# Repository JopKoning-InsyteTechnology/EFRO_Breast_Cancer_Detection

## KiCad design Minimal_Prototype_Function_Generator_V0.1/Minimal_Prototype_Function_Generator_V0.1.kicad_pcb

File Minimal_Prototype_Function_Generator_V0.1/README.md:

# Module README Template

This `README.md` should be placed inside each module folder (e.g., `Sensors/<Type>/<ModuleName>/`).
It documents the changelog, ordering specifications, and module details for that specific PCB.

---

# Module: `<Module Name>`

## 🏷️ Project Status

Choose **one** badge to indicate the current status of the module:

*(Keep only the relevant badge active in the README. Remove the rest.)*

## 📜 Changelog

| Name  | Date       | Version | Updates                                                 |
| ----- | ---------- | ------- | ------------------------------------------------------- |
| Alice | 01/03/2025 | 1.0     | Initial schematic and layout setup                      |
| Bob   | 15/03/2025 | 1.1     | Updated footprint of sensor, adjusted routing           |
| Carol | 25/03/2025 | 1.1.1   | Fixed silkscreen text overlap, added missing test point |

*(Add rows for each update. Follow semantic versioning: Major.Minor.Patch)*

---

## ⚙️ Ordering Specifications

* **Board thickness**: \<e.g., 0.8 mm>
* **Impedance match**: \<Yes/No, Impedance ohm>
* **Impedance Calculated on** \<e.g., JLC04081H-3313>
* **Base material**: \<e.g., FR4>
* **Color**: \<e.g., Green>
* **Outer copper weight**: \<e.g., 1 oz>
* **Gold fingers**: \<Yes/No, Finish type>
* **Castellated holes**: <Yes/No>
* **Edge plating**: \<Yes/No>
* **Assembly side**: \<Top/Bottom/Both>

---

## 🧩 Module Details

* **Sensor description**: <Short functional description>
* **Used voltage**: \<e.g., 3.3V, Battery, 5V>
* **Used interface**: \<e.g., I2C, SPI, ADC>
* **Active power consumption**: \<Value + unit>
* **Max power consumption**: \<Value + unit>
* **Off mode power consumption**: \<Value + unit>

### Pin definitions

* `<Pin name>` → `<Function>`
* `<Pin name>` → `<Function>`

### Other information

* \<Addresses, special notes, mechanical details, etc.>

---

## 📂 Production References

* See related files in `production/Order_<date>`.

---

### Usage Notes

* Keep this file updated with every version change.
* Ensure production orders reference the correct version noted here.
* Use semantic versioning for updates (Major.Minor.Patch).

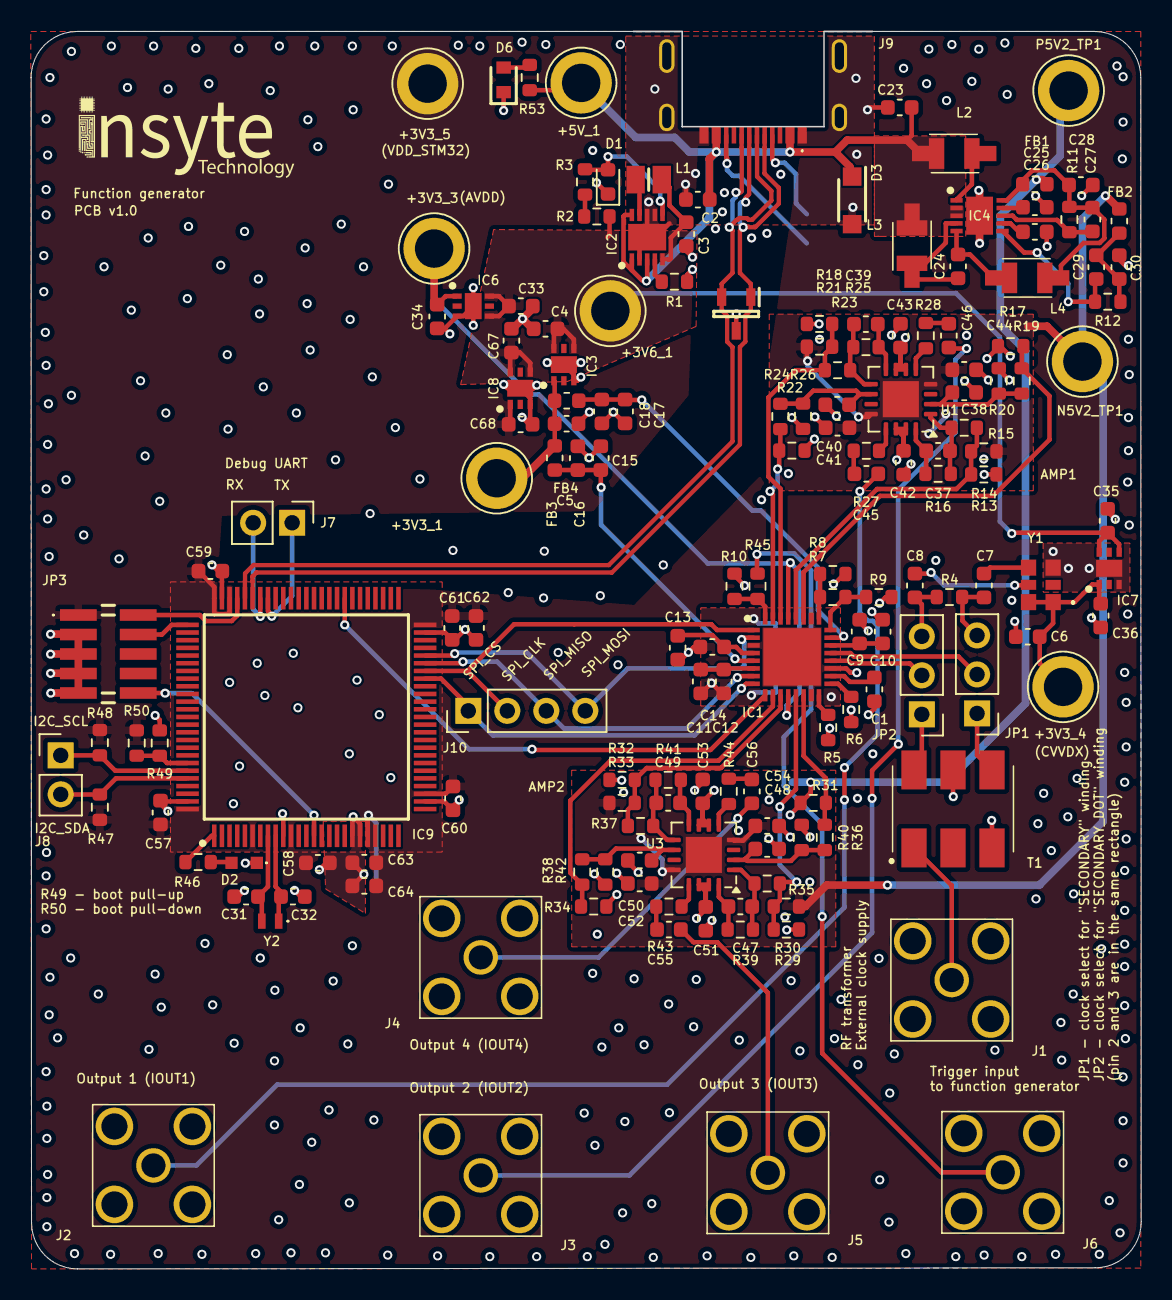
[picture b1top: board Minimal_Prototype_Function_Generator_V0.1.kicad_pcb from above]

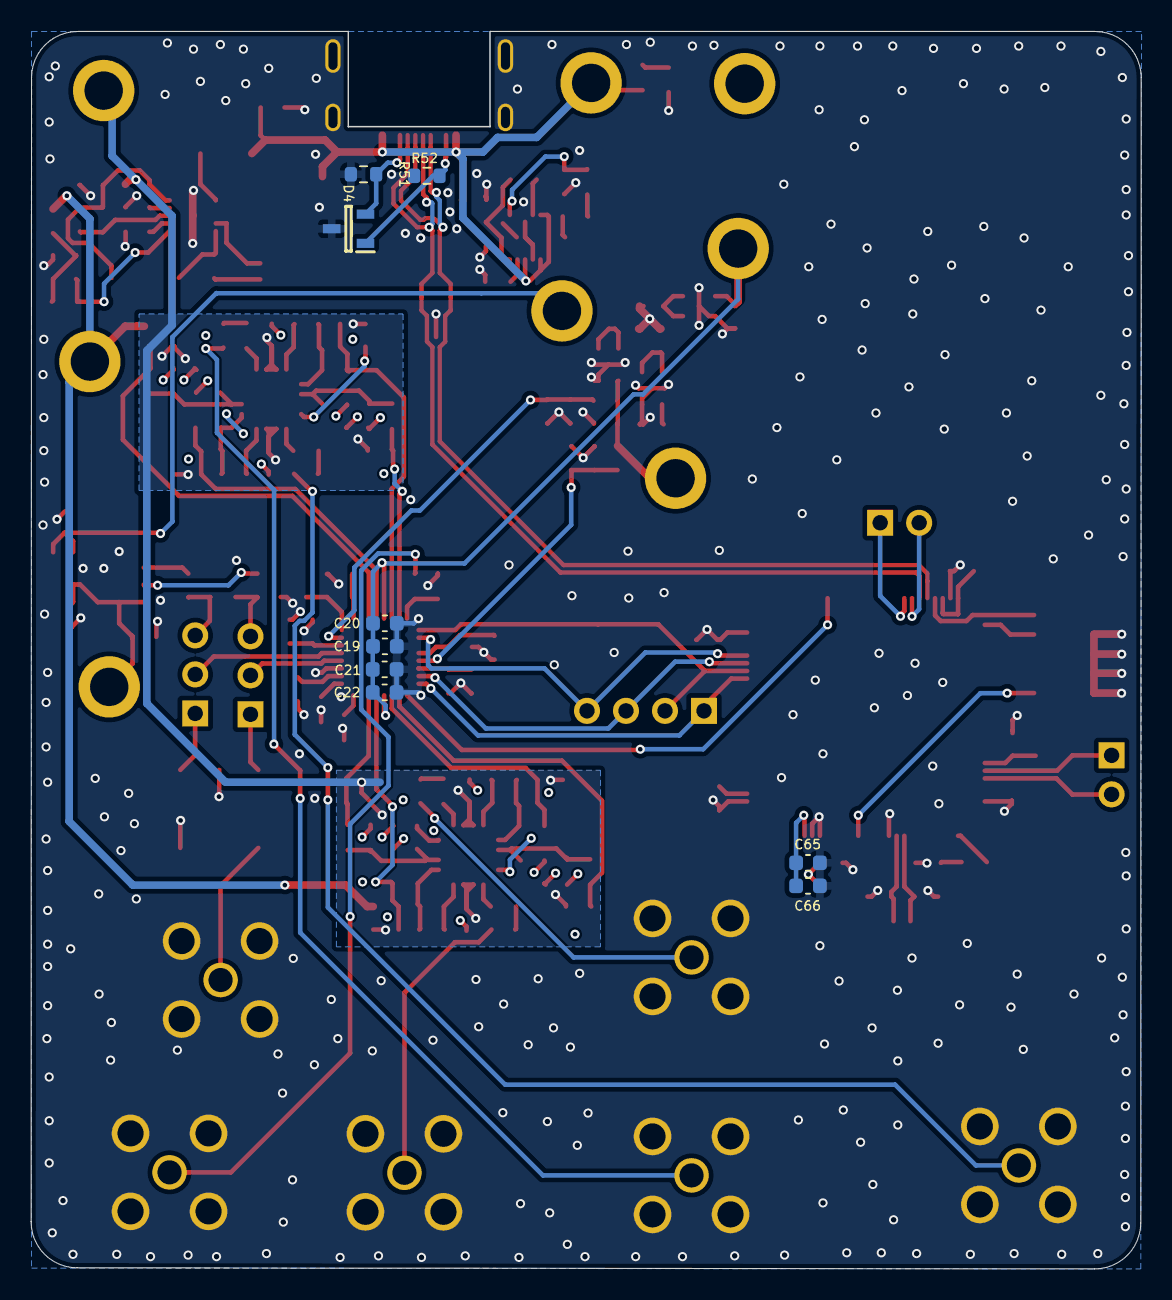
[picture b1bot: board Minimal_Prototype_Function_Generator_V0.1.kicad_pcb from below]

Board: 4 copper layers, 72.3 x 80.6 mm, 170 parts (9 on the bottom side), 97 nets.

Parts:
+3V3_1, +3V3_3, +3V3_4, +3V3_5, +3V6_1, +5V_1: TestPoint; TestPoint_Loop_D3.80mm_Drill2.5mm
C1, C6, C7, C8, C9, C11, C13, C15, C17, C19, C21, C25, C26, C41, C42, C43, C44, C51, C52, C53, C54: 0.1uF; C_0603_1608Metric
C2, C3: 10uF; C_0603_1608Metric
C4, C5, C33, C34, C35, C36, C67, C68: 4.7uF; C_0603_1608Metric
C10, C12, C16, C18, C20, C22: 100pF; C_0603_1608Metric
C14: 0.01uF; C_0603_1608Metric
C23, C28, C30: 2.2uF; C_0603_1608Metric
C24, C45, C46, C55, C56: 1uF; C_0603_1608Metric
C27: 4.7pF; C_0603_1608Metric
C29: 10pF; C_0603_1608Metric
C31, C32: 8pF C0G/NP0 >5%; C_0603_1608Metric
C37, C38, C39, C40, C47, C48, C49, C50: 1.5pF; C_0603_1608Metric
C57, C58, C59, C60, C61, C65: 0.1u; C_0603_1608Metric
C62: 4.7u; C_0603_1608Metric
C63: 0.01u; C_0603_1608Metric
C64, C66: 1u; C_0603_1608Metric
D1: LED GREEN; LED_0603_1608Metric
D2: CSL1901MW1
D3: SMF5.0A; SODFL3618X110N
D4, D5: SM05.TCT; SOT95P237X125-3N
D6: APT1608LZGCK; LEDC1608X85N
FB1, FB2, FB3, FB4: 1.8K OHM AT 100MEGHZ; L_0603_1608Metric
IC1: AD9106BCPZ; QFN50P500X500X80-33N-D
IC2: ADP5300ACPZ-1-R7; SON50P300X300X85-11N-D
IC3, IC6, IC7, IC8: ADM7160ACPZN3.3-R7; SON65P200X200X65-7N-D
IC4: LT3472EDD#PBF; SON50P300X300X80-11N-D
IC9: STM32L476VGT6; QFP50P1600X1600X160-100N
J1, J2, J3, J4, J5, J6: 142-0701-201; 1420701201
J7: DEBUG_UART_TP_1; PinHeader_1x02_P2.54mm_Vertical
J8: I2C_TP1; PinHeader_1x02_P2.54mm_Vertical
J9: USB4500-03-0-A; USB4500030A
J10: SPI_TP_1; PinHeader_1x04_P2.54mm_Vertical
JP1, JP2: Jumper_3_Open; PinHeader_1x03_P2.54mm_Vertical
JP3: 20021121-00010C4LF; 2002112100010C4LF
L1: MLP2016H2R2MT0S1; INDC2016X100N
L2: 22uH; LQH32CH100K53L
L3, L4: 47uH; LQH32CH100K53L
N5V2_TP1: TestPoint; TestPoint_Loop_D3.80mm_Drill2.5mm
P5V2_TP1: TestPoint; TestPoint_Loop_D3.80mm_Drill2.5mm
R1: 499K; R_0603_1608Metric
R2, R4: 100R; R_0603_1608Metric
R3, R7: 0R; R_0603_1608Metric
R5, R6, R8, R9: 8.06K; R_0603_1608Metric
R10: 9.1K; R_0603_1608Metric
R11: 158K; R_0603_1608Metric
R12: 210K; R_0603_1608Metric
R13, R14, R17, R18, R21, R22, R29, R30, R31, R32, R33, R34: 1K; R_0603_1608Metric
R15, R16, R19, R20, R23, R24, R25, R26, R35, R36, R37, R38, R39, R40, R41, R42: 499R; R_0603_1608Metric
R27, R28, R43, R44: 49.9R; R_0603_1608Metric
R45: 4.7K; R_0603_1608Metric
R46: 750; R_0603_1608Metric
R47, R48: 4K7; R_0603_1608Metric
R49, R50: 10K; R_0603_1608Metric
R51, R52: 5.1K; R_0603_1608Metric
R53: 325R; R_0603_1608Metric
T1: ADT2-1T+; ADT21T
U1, U3: ADA4817-2ACP; Analog_LFCSP-16-1EP_4x4mm_P0.65mm_EP2.35x2.35mm
U4: 15x6_Insyte_Logo
Y1: AX3DCF1-156.2500T; AX3_3.2x2.5
Y2: ECS-.327-7-16-C-TR; ECS327516TR

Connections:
/Function Generator/!RESET: IC1.9 (~RESET), IC9.58 (PD11)
/Function Generator/AVDD: +3V3_3.1, C19.1, C20.1, C21.1, C22.1, C34.1, IC1.12 (AVDD2), IC1.29 (AVDD1), IC6.1 (VOUT)
/Function Generator/CLKLDO: C9.1, C10.1, IC1.22 (CLDO)
/Function Generator/CLKN: IC1.20 (CLKN), JP2.2 (C)
/Function Generator/CLKP: IC1.21 (CLKP), JP1.2 (C)
/Function Generator/CLKVDD: C17.1, C18.1, FB4.2, IC1.23 (CLKVDD)
/Function Generator/CVDDX: +3V3_4.1, C6.1, C36.1, IC7.1 (VOUT), Y1.1 (E/D), Y1.6 (VDD)
/Function Generator/DLDO1: C11.1, C12.1, IC1.6 (DLDO1)
/Function Generator/DLDO2: C13.1, C14.1, IC1.4 (DLDO2)
/Function Generator/DVDD: C15.1, C16.1, FB3.2, IC1.5 (DVDD)
/Function Generator/I_Out_N1: IC1.28 (IOUTN1), R13.1, R14.2, R15.2
/Function Generator/I_Out_N2: IC1.30 (IOUTN2), R18.1, R21.2, R23.2
/Function Generator/I_Out_N3: IC1.13 (IOUTN3), R29.1, R30.2, R35.2
/Function Generator/I_Out_N4: IC1.11 (IOUTN4), R32.1, R33.2, R37.2
/Function Generator/I_Out_P1: IC1.27 (IOUTP1), R17.1, R19.2
/Function Generator/I_Out_P2: IC1.31 (IOUTP2), R22.1, R24.2
/Function Generator/I_Out_P3: IC1.14 (IOUTP3), R31.1, R36.2
/Function Generator/I_Out_P4: IC1.10 (IOUTP4), R34.1, R38.2
/Function Generator/SPI_CLK: IC1.1 (SCLK), IC9.44 (PE13), J10.2
/Function Generator/SPI_CS: IC1.8 (~CS), IC9.43 (PE12), J10.1
/Function Generator/SPI_MISO: IC1.7 (SDO/SDI2/DOUT), IC9.45 (PE14), J10.3
/Function Generator/SPI_MOSI: IC1.2 (SDIO), IC9.46 (PE15), J10.4
/Function Generator/Trigger_Input_3V3: IC1.32 (~TRIGGER), R10.2, R45.1
/Output_Stage/N5V2: C41.1, C44.1, C52.1, C54.1, FB2.2, N5V2_TP1.1, R14.1, R21.1, R30.1, R33.1, U1.4 (-V_{S}), U1.12 (-V_{S}), U1.17 (EP), U3.4 (-V_{S}), U3.12 (-V_{S}), U3.17 (EP)
/Output_Stage/Op_Amp_1/+IN_1: C38.1, R19.1, R20.1, U1.2 (+)
/Output_Stage/Op_Amp_1/+IN_2: C40.1, R24.1, R26.1, U1.10 (+)
/Output_Stage/Op_Amp_1/-IN_1: C37.1, R15.1, R16.1, U1.1 (-)
/Output_Stage/Op_Amp_1/-IN_2: C39.1, R23.1, R25.1, U1.9 (-)
/Output_Stage/Op_Amp_1/AMP1_OUT: C46.2, J3.1 (In)
/Output_Stage/Op_Amp_1/AMP_OUT: C45.2, J2.1 (In)
/Output_Stage/Op_Amp_1/FB_1: C37.2, R16.2, U1.16 (FB)
/Output_Stage/Op_Amp_1/FB_2: C39.2, R25.2, U1.8 (FB)
/Output_Stage/Op_Amp_2/+IN_1: C48.1, R36.1, R40.1, U3.2 (+)
/Output_Stage/Op_Amp_2/+IN_2: C50.1, R38.1, R42.1, U3.10 (+)
/Output_Stage/Op_Amp_2/-IN_1: C47.1, R35.1, R39.1, U3.1 (-)
/Output_Stage/Op_Amp_2/-IN_2: C49.1, R37.1, R41.1, U3.9 (-)
/Output_Stage/Op_Amp_2/AMP1_OUT: C56.2, J4.1 (In)
/Output_Stage/Op_Amp_2/AMP_OUT: C55.2, J5.1 (In)
/Output_Stage/Op_Amp_2/FB_1: C47.2, R39.2, U3.16 (FB)
/Output_Stage/Op_Amp_2/FB_2: C49.2, R41.2, U3.8 (FB)
/Output_Stage/P5V2: C42.2, C43.2, C51.2, C53.2, FB1.2, P5V2_TP1.1, R13.2, R17.2, R18.2, R22.2, R29.2, R31.2, R32.2, R34.2, U1.6 (+V_{S}), U1.7 (~PD), U1.14 (+V_{S}), U1.15 (~PD), U3.6 (+V_{S}), U3.7 (~PD), U3.14 (+V_{S}), U3.15 (~PD)
/Power/5V: +5V_1.1, C2.1, C23.1, D3.1 (K), IC2.1 (EN), IC2.3 (SYNC/MODE), IC2.10 (PVIN), IC4.2 (VIN), IC4.3 (~SHDN), J9.A4 (VBUS_1), J9.A9 (VBUS_2), L2.1, L2.3, L3.2, L3.4, R53.1
/Power/ADM7160ACPZN3.3_1/+3V3: +3V3_1.1, C5.1, FB3.1, FB4.1, IC3.1 (VOUT)
/Power/ADM7160ACPZN3.3_1/+3V6: +3V6_1.1, C3.1, C4.1, C33.1, C35.1, C67.1, IC2.5 (FB), IC3.4 (EN), IC3.6 (VIN), IC6.4 (EN), IC6.6 (VIN), IC7.4 (EN), IC7.6 (VIN), IC8.4 (EN), IC8.6 (VIN), L1.2, R2.1
/Power/LT3472EDD/N5V2_VN: C29.2, C30.1, FB2.1, R12.2
/Power/LT3472EDD/P5V2_VP: C27.2, C28.1, FB1.1, IC4.10 (VPOS), L4.1, L4.3, R11.2
/Power/VDD_STM32: +3V3_5.1, C57.1, C58.1, C59.1, C60.1, C61.1, C62.1, C63.1, C64.1, C65.1, C66.1, C68.1, IC8.1 (VOUT), IC9.6 (VBAT), IC9.11 (VDD_1), IC9.21 (VREF+), IC9.22 (VDDA), IC9.28 (VDD_2), IC9.50 (VDD_3), IC9.73 (VDDUSB), IC9.75 (VDD_4), IC9.100 (VDD_5), JP3.1, R47.1, R48.1, R50.1
/STM32/I2C_SCL: IC9.95 (PB8), J8.1, R48.2
/STM32/I2C_SDA: IC9.96 (PB9), J8.2, R47.2
/STM32/NRST: IC9.14 (NRST), JP3.10
/STM32/SWCLK: IC9.76 (PA14), JP3.4
/STM32/SWDIO: IC9.72 (PA13), JP3.2
/USB_C/CC1: D4.2 (K), J9.A5 (CC1), R51.1
/USB_C/CC2: D4.1 (K), J9.B5 (CC2), R52.1
/USB_C/D+: D5.2 (K), IC9.71 (PA12), J9.A6 (DP1), J9.B6 (DP2)
/USB_C/D-: D5.1 (K), IC9.70 (PA11), J9.A7 (DN1), J9.B7 (DN2)
GND: C1.2, C2.2, C3.2, C4.2, C5.2, C6.2, C9.2, C10.2, C11.2, C12.2, C13.2, C14.2, C15.2, C16.2, C17.2, C18.2, C19.2, C20.2, C21.2, C22.2, C23.2, C25.2, C26.2, C28.2, C30.2, C31.1, C32.1, C33.2, C34.2, C35.2, C36.2, C38.2, C40.2, C41.2, C42.1, C43.1, C44.2, C48.2, C50.2, C51.1, C52.2, C53.1, C54.2, C57.2, C58.2, C59.2, C60.2, C61.2, C62.2, C63.2, C64.2, C65.2, C66.2, C67.2, C68.2, D1.1 (K), D2.1 (K), D3.2 (A), D4.3 (A), D5.3 (A), D6.1 (K), IC1.3 (DGND), IC1.15 (AGND_1), IC1.19 (CLKGND), IC1.26 (AGND_2), IC1.33 (GND), IC2.2 (STOP), IC2.7 (AGND), IC2.8 (PGND), IC2.11 (EP), IC3.3 (GND), IC3.7 (EP), IC4.11 (EP), IC6.3 (GND), IC6.7 (EP), IC7.3 (GND), IC7.7 (EP), IC8.3 (GND), IC8.7 (EP), IC9.10 (VSS_1), IC9.19 (VSSA), IC9.20 (VREF-), IC9.27 (VSS_2), IC9.49 (VSS_3), IC9.74 (VSS_4), IC9.99 (VSS_5), J1.2 (Ext), J1.3 (Ext), J1.4 (Ext), J1.5 (Ext), J2.2 (Ext), J2.3 (Ext), J2.4 (Ext), J2.5 (Ext), J3.2 (Ext), J3.3 (Ext), J3.4 (Ext), J3.5 (Ext), J4.2 (Ext), J4.3 (Ext), J4.4 (Ext), J4.5 (Ext), J5.2 (Ext), J5.3 (Ext), J5.4 (Ext), J5.5 (Ext), J6.2 (Ext), J6.3 (Ext), J6.4 (Ext), J6.5 (Ext), J9.A1 (GND_1), J9.A12 (GND_2), J9.MH1, J9.MH2, J9.MH3, J9.MH4, JP3.3, JP3.5, JP3.7, JP3.9, R1.2, R5.2, R6.2, R8.1, R9.1, R10.1, R20.2, R26.2, R40.2, R42.2, R49.2, R51.2, R52.2, T1.3 (PRIMARY_DOT), T1.5 (SECONDARY_CT), Y1.3 (GND)
unnamed: C45.1, R27.1
unnamed: C46.1, R28.1
unnamed: C55.1, R43.1
unnamed: C56.1, R44.1
unnamed: D1.2 (A), IC2.6 (VOUTOK), R3.2
unnamed: D2.2 (A), R46.2
unnamed: D6.2 (A), R53.2
unnamed: IC1.25 (FSADJ1), R7.1, R8.2
unnamed: IC1.24 (FSADJ2/CAL_SENSE), R7.2, R9.2
unnamed: IC1.16 (FSADJ3), R5.1
unnamed: IC1.17 (FSADJ4), R6.1
unnamed: C1.1, IC1.18 (REFIO)
unnamed: IC2.9 (SW), L1.1
unnamed: IC2.4 (VID), R1.1
unnamed: C24.2, IC4.5 (DN), L4.2, L4.4
unnamed: C29.1, IC4.6 (FBN), R12.1
unnamed: C27.1, IC4.8 (FBP), R11.1
unnamed: C26.1, IC4.7 (SSN)
unnamed: C25.1, IC4.9 (SSP)
unnamed: C24.1, IC4.4 (SWN), L3.1, L3.3
unnamed: IC4.1 (SWP), L2.2, L2.4
unnamed: IC9.94 (BOOT0), R49.1, R50.2
unnamed: IC9.68 (PA9), J7.1
unnamed: IC9.69 (PA10), J7.2
unnamed: C31.2, IC9.8 (PC14/OSC32_IN), Y2.2 (OUT/IN)
unnamed: C32.2, IC9.9 (PC15/OSC32_OUT), Y2.1
unnamed: IC9.1 (PE2), R46.1
unnamed: J1.1 (In), T1.1 (PRIMARY)
unnamed: J6.1 (In), R45.2
unnamed: JP1.1 (A), T1.4 (SECONDARY)
unnamed: C7.2, JP1.3 (B), R4.1
unnamed: JP2.1 (A), T1.6 (SECONDARY_DOT)
unnamed: C8.2, JP2.3 (B), R4.2
unnamed: R2.2, R3.1
unnamed: R27.2, U1.13
unnamed: R28.2, U1.5
unnamed: R43.2, U3.13
unnamed: R44.2, U3.5
unnamed: C8.1, Y1.5 (COMP_OUT)
unnamed: C7.1, Y1.4 (OUTPUT)

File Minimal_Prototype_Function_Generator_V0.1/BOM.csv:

"Reference","Value","Datasheet","Footprint","Qty","DNP"
"+3V3_1,+3V3_3,+3V3_4,+3V3_5,+3V6_1,+5V_1,N5V2_TP1,P5V2_TP1","TestPoint","~","TestPoint:TestPoint_Loop_D3.80mm_Drill2.5mm","8",""
"C1,C6,C7,C8,C9,C11,C13,C15,C17,C19,C21,C25,C26,C41,C42,C43,C44,C51,C52,C53,C54","0.1uF","~","Capacitor_SMD:C_0603_1608Metric","21",""
"C2,C3","10uF","~","Capacitor_SMD:C_0603_1608Metric","2",""
"C4,C5,C33,C34,C35,C36,C67,C68","4.7uF","~","Capacitor_SMD:C_0603_1608Metric","8",""
"C10,C12,C16,C18,C20,C22","100pF","~","Capacitor_SMD:C_0603_1608Metric","6",""
"C14","0.01uF","~","Capacitor_SMD:C_0603_1608Metric","1",""
"C23,C28,C30","2.2uF","~","Capacitor_SMD:C_0603_1608Metric","3",""
"C24,C45,C46,C55,C56","1uF","~","Capacitor_SMD:C_0603_1608Metric","5",""
"C27","4.7pF","~","Capacitor_SMD:C_0603_1608Metric","1",""
"C29","10pF","~","Capacitor_SMD:C_0603_1608Metric","1",""
"C31,C32","8pF C0G/NP0  >5%","~","Capacitor_SMD:C_0603_1608Metric","2",""
"C37,C38,C39,C40,C47,C48,C49,C50","1.5pF","~","Capacitor_SMD:C_0603_1608Metric","8",""
"C57,C58,C59,C60,C61,C65","0.1u","~","Capacitor_SMD:C_0603_1608Metric","6",""
"C62","4.7u","~","Capacitor_SMD:C_0603_1608Metric","1",""
"C63","0.01u","~","Capacitor_SMD:C_0603_1608Metric","1",""
"C64,C66","1u","~","Capacitor_SMD:C_0603_1608Metric","2",""
"D1","LED GREEN","~","LED_SMD:LED_0603_1608Metric","1",""
"D2","CSL1901MW1","https://fscdn.rohm.com/en/products/databook/datasheet/opto/l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","Insyte_Footprints:CSL1901MW1","1",""
"D3","SMF5.0A","~","Insyte_Footprints:SODFL3618X110N","1",""
"D4,D5","SM05.TCT","","Insyte_Footprints:SOT95P237X125-3N","2",""
"D6","APT1608LZGCK","~","Insyte_Footprints:LEDC1608X85N","1",""
"FB1,FB2,FB3,FB4","1.8K OHM AT 100MEGHZ","~","Inductor_SMD:L_0603_1608Metric","4",""
"IC1","AD9106BCPZ","https://www.analog.com/AD9106/datasheet","Insyte_Footprints:QFN50P500X500X80-33N-D","1",""
"IC2","ADP5300ACPZ-1-R7","https://componentsearchengine.com/Datasheets/1/ADP5300ACPZ-1-R7.pdf","Insyte_Footprints:SON50P300X300X85-11N-D","1",""
"IC3,IC6,IC7,IC8","ADM7160ACPZN3.3-R7","https://componentsearchengine.com/Datasheets/1/ADM7160ACPZN3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","Insyte_Footprints:SON65P200X200X65-7N-D","4",""
"IC4","LT3472EDD#PBF","https://www.analog.com/media/en/technical-documentation/data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","Insyte_Footprints:SON50P300X300X80-11N-D","1",""
"IC9","STM32L476VGT6","https://datasheet.datasheetarchive.com/originals/distributor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","Insyte_Footprints:QFP50P1600X1600X160-100N","1",""
"J1,J2,J3,J4,J5,J6","142-0701-201","https://datasheet.datasheetarchive.com/originals/distributor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","Insyte_Footprints:1420701201","6",""
"J7","DEBUG_UART_TP_1","~","Connector_PinHeader_2.54mm:PinHeader_1x02_P2.54mm_Vertical","1",""
"J8","I2C_TP1","~","Connector_PinHeader_2.54mm:PinHeader_1x02_P2.54mm_Vertical","1",""
"J9","USB4500-03-0-A","https://componentsearchengine.com/Datasheets/2/USB4500-03-0-A.pdf","Insyte_Footprints:USB4500030A","1",""
"J10","SPI_TP_1","~","Connector_PinHeader_2.54mm:PinHeader_1x04_P2.54mm_Vertical","1",""
"JP1,JP2","Jumper_3_Open","~","Connector_PinHeader_2.54mm:PinHeader_1x03_P2.54mm_Vertical","2",""
"JP3","20021121-00010C4LF","","Insyte_Footprints:2002112100010C4LF","1",""
"L1","MLP2016H2R2MT0S1","https://product.tdk.com/system/files/dam/doc/product/inducto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","Insyte_Footprints:INDC2016X100N","1",""
"L2","22uH","https://search.murata.co.jp/Ceramy/image/img/P02/JELF243A-0030.pdf","Insyte_Footprints:LQH32CH100K53L","1",""
"L3,L4","47uH","https://search.murata.co.jp/Ceramy/image/img/P02/JELF243A-0030.pdf","Insyte_Footprints:LQH32CH100K53L","2",""
"R1","499K","~","Resistor_SMD:R_0603_1608Metric","1",""
"R2,R4","100R","~","Resistor_SMD:R_0603_1608Metric","2",""
"R3,R7","0R","~","Resistor_SMD:R_0603_1608Metric","2",""
"R5,R6,R8,R9","8.06K","~","Resistor_SMD:R_0603_1608Metric","4",""
"R10","9.1K","~","Resistor_SMD:R_0603_1608Metric","1",""
"R11","158K","~","Resistor_SMD:R_0603_1608Metric","1",""
"R12","210K","~","Resistor_SMD:R_0603_1608Metric","1",""
"R13,R14,R17,R18,R21,R22,R29,R30,R31,R32,R33,R34","1K","~","Resistor_SMD:R_0603_1608Metric","12",""
"R15,R16,R19,R20,R23,R24,R25,R26,R35,R36,R37,R38,R39,R40,R41,R42","499R","~","Resistor_SMD:R_0603_1608Metric","16",""
"R27,R28,R43,R44","49.9R","~","Resistor_SMD:R_0603_1608Metric","4",""
"R45","4.7K","~","Resistor_SMD:R_0603_1608Metric","1",""
"R46","750","~","Resistor_SMD:R_0603_1608Metric","1",""
"R47,R48","4K7","~","Resistor_SMD:R_0603_1608Metric","2",""
"R49","10K","~","Resistor_SMD:R_0603_1608Metric","1",""
"R50","10K","~","Resistor_SMD:R_0603_1608Metric","1","DNP"
"R51,R52","5.1K","~","Resistor_SMD:R_0603_1608Metric","2",""
"R53","325R","~","Resistor_SMD:R_0603_1608Metric","1",""
"TR1","ADT2-1T","https://www.minicircuits.com/pdfs/ADT2-1T+.pdf","RF_Mini-Circuits:Mini-Circuits_CD542_H2.84mm","1",""
"U1,U3","ADA4817-2ACP","https://www.analog.com/media/en/technical-documentation/data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","Package_CSP:Analog_LFCSP-16-1EP_4x4mm_P0.65mm_EP2.35x2.35mm","2",""
"Y1","AX3DCF1-156.2500T","https://abracon.com/datasheets/AX3.pdf","Insyte_Footprints:AX3_3.2x2.5","1",""
"Y2","ECS-.327-7-16-C-TR","","Insyte_Footprints:ECS327516TR","1",""

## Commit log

2025-09-08 First schematic
2025-09-09 Routing PCB, not yet finished
2025-09-10 Preliminary delivery of PCB, v0.1
2025-09-11 PCB delivery, v1.0
2025-09-11 Removed backups from remote
2025-09-12 Added schematic documentation
2025-09-15 Implemented almost all feedback
2025-09-15 Updated schemattic documentation
2025-09-15 Updated PCB and schematic, according to feedback
2025-09-23 Ready for order
2025-09-29 Added info on impedance matching
2025-09-29 Order
